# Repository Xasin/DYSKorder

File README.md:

# DYSKorder
What happens if you slap together the Apollo Guidance interface and a few StarTrek inspired interfaces? We'll see!

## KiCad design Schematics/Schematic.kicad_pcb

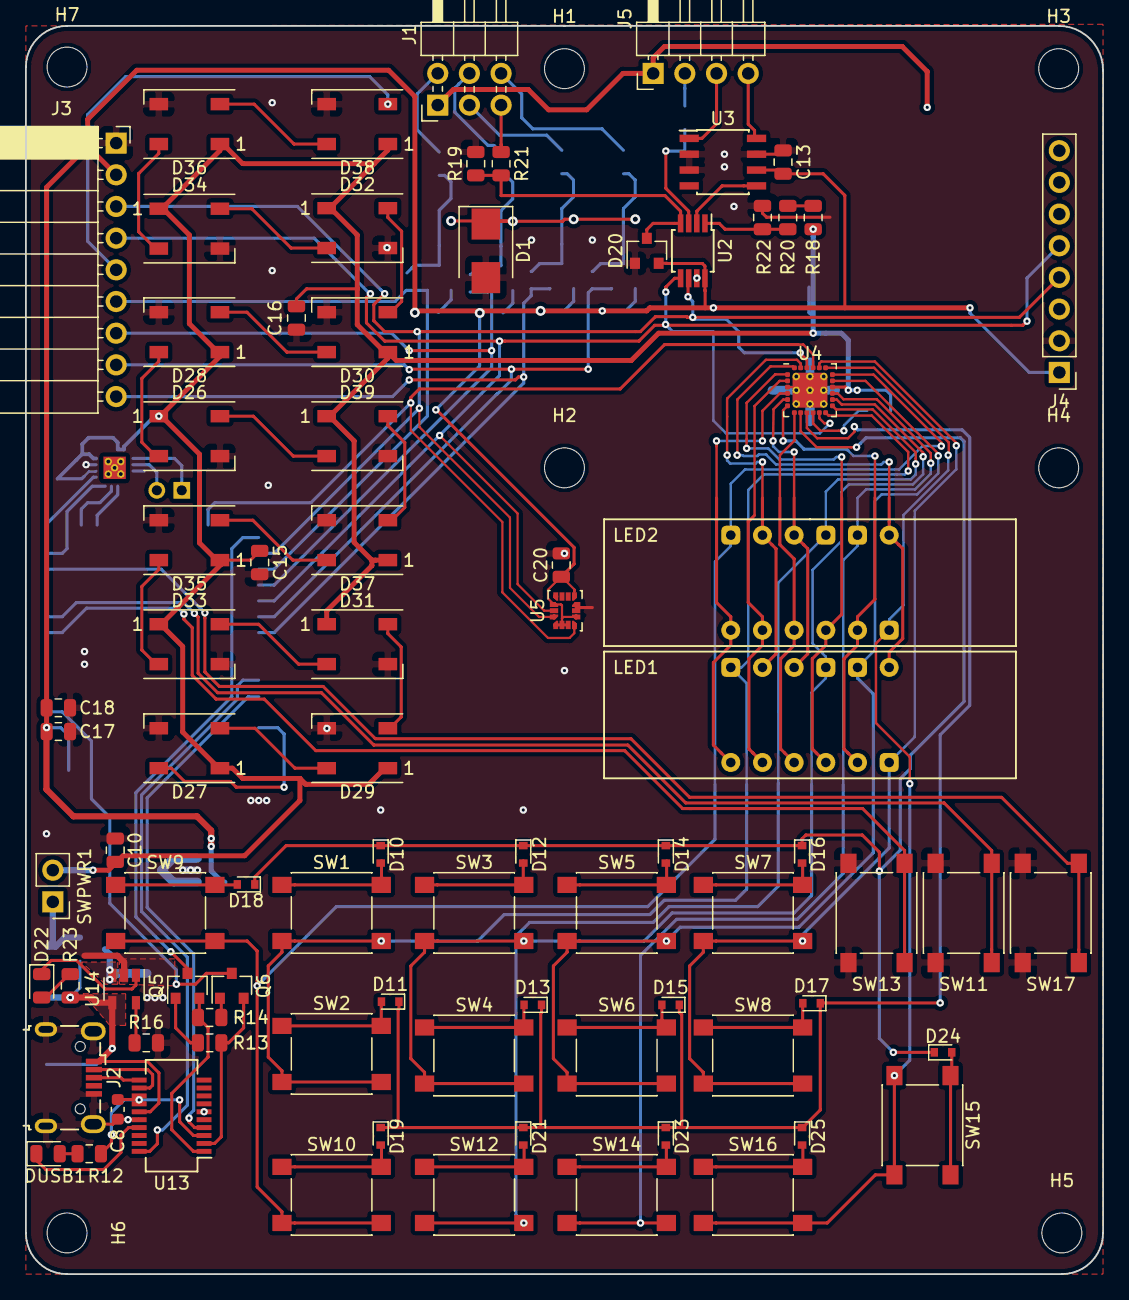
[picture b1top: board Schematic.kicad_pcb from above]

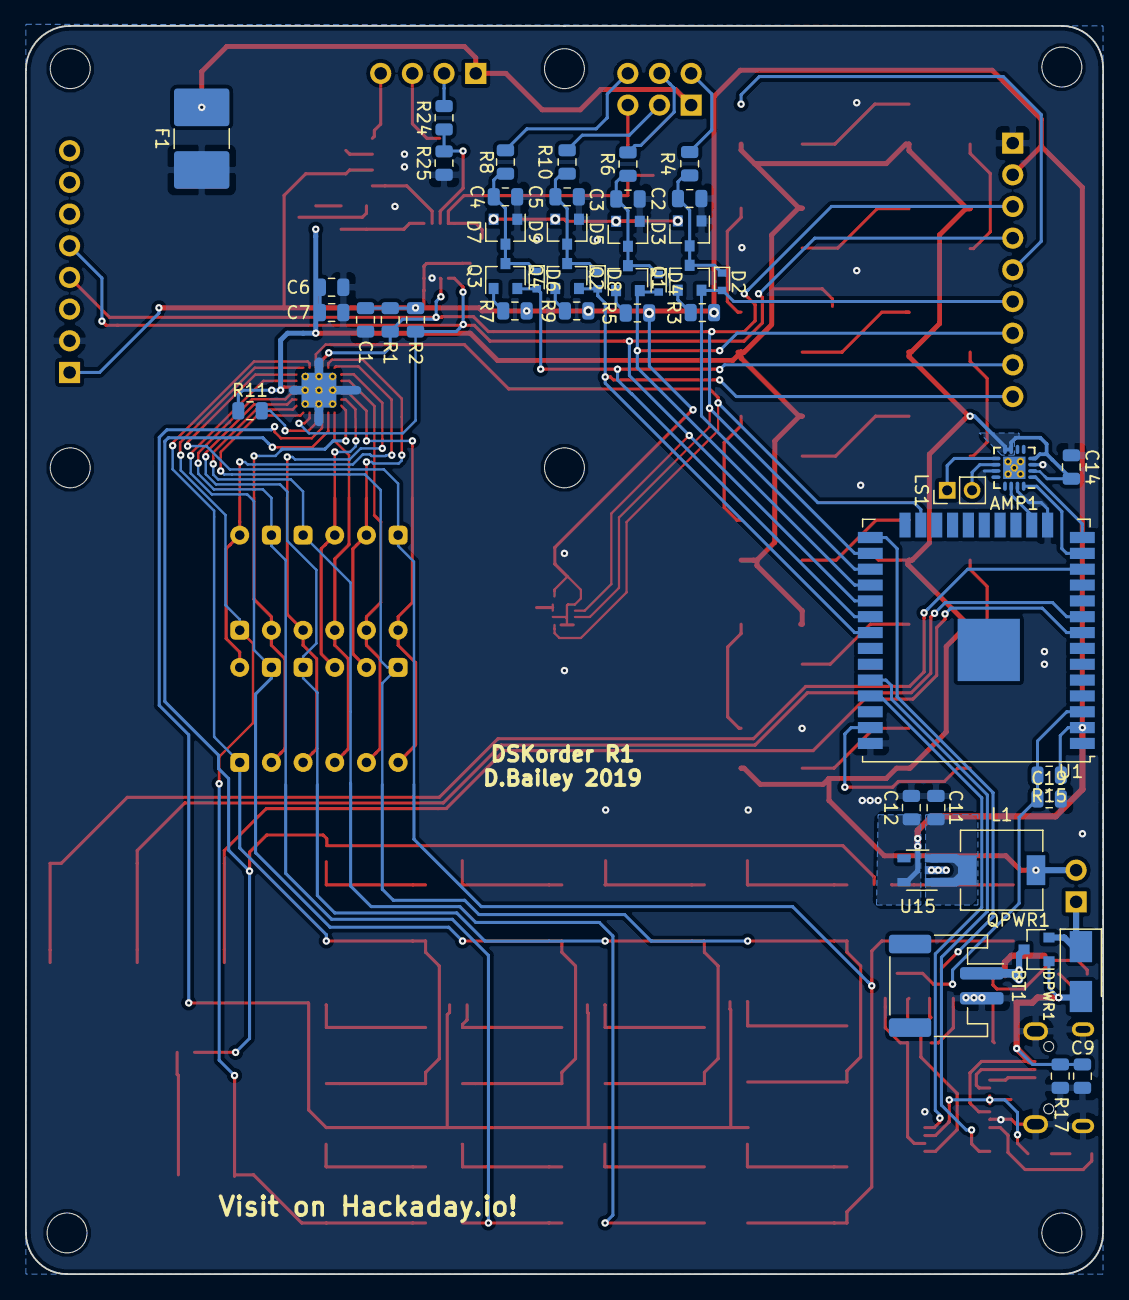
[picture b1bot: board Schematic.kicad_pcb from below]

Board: 2 copper layers, 86.4 x 100.1 mm, 140 parts (50 on the bottom side), 109 nets.

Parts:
AMP1: MAX98357A; QFN-16-1EP_3x3mm_P0.5mm_EP2.7x2.7mm_ThermalVias
BT1: Battery_Cell; JST_PH_S2B-PH-SM4-TB_1x02-1MP_P2.00mm_Horizontal
C1, C6, C13, C15, C16, C18, C20: 0.1uF; C_0805_2012Metric
C2, C3, C4, C5: C_Small; C_0805_2012Metric
C7, C9, C10, C12, C17: 10uF; C_0805_2012Metric
C8: 150nF; C_0603_1608Metric
C11: 150nF; C_0805_2012Metric
C14: 1uF; C_0805_2012Metric
C19: 100nF; C_0805_2012Metric
D1: 14V Breakdown; D_SMB
D2, D4, D6, D8: D_Schottky; D_SOD-523
D3, D5, D7, D9, D20: DB3X313F; SOT-23
D10, D11, D12, D13, D14, D15, D16, D17, D18, D19, D23, D24, D25: D_Small; D_SOD-523
D21: RB521S30T1GOSCT-ND; D_SOD-523
D22: LED; LED_0805_2012Metric
D26, D27, D28, D29, D30, D31, D32, D33, D34, D35, D36, D37, D38, D39: WS2812B; LED_WS2812B_PLCC4_5.0x5.0mm_P3.2mm
DPWR1: D_Schottky; D_SMA
DUSB1: LED; LED_0805_2012Metric
F1: Fuse_Small; Fuse_2816_7142Metric
H1, H2, H3, H4, H5, H6, H7: MountingHole; MountingHole_3.2mm_M3
J1: Conn_02x03_Odd_Even; PinHeader_2x03_P2.54mm_Horizontal
J2: USB_B_Micro; USB_Micro-B_Wuerth_629105150521
J3: Conn_01x09_Female; PinSocket_1x09_P2.54mm_Horizontal
J4: Conn_01x08_Male; PinHeader_1x08_P2.54mm_Vertical
J5: Conn_01x04_Male; PinHeader_1x04_P2.54mm_Horizontal
L1: 100uH; L_6.3x6.3_H3
LED1, LED2: LDQ-M282RI
LS1: Speaker; PinHeader_1x02_P2.00mm_Vertical
Q1, Q2, Q3, Q4, Q5, Q6: Q_NPN_BEC; SOT-23
QPWR1: IRLML6402; SOT-23
R1, R13, R14, R15: R_Small; R_0805_2012Metric
R2, R3, R5, R7, R9, R16, R17: 10k; R_0805_2012Metric
R4, R6, R8, R10, R23: 100R; R_0805_2012Metric
R11: >25k; R_0805_2012Metric
R12: 220; R_0805_2012Metric
R18, R20, R22: 100k; R_0805_2012Metric
R19: 2k; R_0805_2012Metric
R21: 8k; R_0805_2012Metric
R24: 43k; R_0805_2012Metric
R25: 4; R_0805_2012Metric
SW1, SW2, SW3, SW4, SW5, SW6, SW7, SW8, SW9, SW10, SW11, SW12, SW13, SW14, SW15, SW16, SW17: Push; SW_SPST_PTS645
SWPWR1: SW_SPST; PinHeader_1x02_P2.54mm_Vertical
SYM1: SYM_Radioactive_Large; Xas_Logo
SYM2: SYM_Radioactive_Large; Hackaday_Link
U1: ESP32-WROOM-32D; ESP32-WROOM-32U
U2: MAX11613; MSOP-8_3x3mm_P0.65mm
U3: AD8418; SOIC-8_3.9x4.9mm_P1.27mm
U4: AS1115-BQFT; TQFN-24-1EP_4x4mm_P0.5mm_EP2.8x2.8mm_PullBack_ThermalVias
U5: LSM6DS3; LGA-14_3x2.5mm_P0.5mm_LayoutBorder3x4y
U13: FT231XS; SSOP-20_3.9x8.7mm_P0.635mm
U14: MCP73832T-2ACI/OTCT-ND; SOT-23-5
U15: SPX3819M5-L-3-3; SOT-23-5

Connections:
+3V3: C1.1, C12.1, C13.2, C17.1, C18.1, C20.1, D20.2, J3.2, J4.1, R1.1, R2.1, R3.1, R5.1, R7.1, R9.1, R15.1, U1.2, U2.8, U3.6, U5.1, U5.2, U5.3, U5.5, U5.8, U5.12, U15.5
+12P: D1.1, D3.2, D5.2, D7.2, D9.2
+BATT: AMP1.2, AMP1.4, AMP1.7, AMP1.8, C6.1, C7.1, C10.1, C14.2, C15.1, C16.1, D26.1, D27.1, D28.1, D29.1, D30.1, D31.1, D32.1, D33.1, D34.1, D35.1, D36.1, D37.1, D38.1, D39.1, L1.2, R11.1, R18.1, SWPWR1.2, U4.16
/BCLK: AMP1.16, U1.13
/BMode1: SW17.2, U1.12
/BMode2: SW13.2, U1.8
/BMode3: SW11.2, U1.9
/Bat_CHG: R20.2, R22.1, U2.1
/DATA: AMP1.1, U1.14
/E>USB: U1.35, U13.4
/GPIO0: Q5.3, U1.25
/IOGate/UPEXT_BAT: J5.2, R24.2
/IOGate/UPEXT_U: J1.5, R21.1
/IOGate/UPIO1: J1.2, R4.1
/IOGate/UPIO2: J1.4, R6.1
/IOGate/UPIO3: J1.6, R8.1
/IOGate/UPIO4: J1.3, R10.1
/IOGate/UP_GND: F1.2, J1.1, J5.1
/LRCLK: AMP1.14, U1.16
/Power Handling/B_Raw+: BT1.1, QPWR1.3, U14.3
/Power Handling/CHG_Stat: D22.1, U14.1
/RESET: C19.1, Q6.3, R15.2, U1.3
/USB Connection/+5V_USB: C9.2, DPWR1.2, J2.1, QPWR1.1, R17.1, R23.1, U13.15, U14.4
/USB Connection/USB3.3: C8.2, R12.1, U13.3, U13.13, U13.14
/USB>E: U1.34, U13.20
/WS2812_OUT: D27.4, U1.37
BTN_IRQ: U1.23, U4.21, U5.4
GND: AMP1.3, AMP1.11, AMP1.15, BT1.2, C1.2, C2.2, C3.2, C4.2, C5.2, C6.2, C7.2, C8.1, C9.1, C10.2, C11.2, C12.2, C13.1, C14.1, C15.2, C16.2, C17.2, C18.2, C19.2, C20.2, D1.2, D3.1, D5.1, D7.1, D9.1, D20.1, D26.3, D27.3, D28.3, D29.3, D30.3, D31.3, D32.3, D33.3, D34.3, D35.3, D36.3, D37.3, D38.3, D39.3, F1.1, J2.5, J2.6, J3.1, J4.2, R16.2, R17.2, R19.2, R22.2, R25.1, SW11.1, SW13.1, SW17.1, U1.1, U1.15, U1.38, U2.7, U3.2, U3.3, U3.7, U4.3, U4.25, U5.6, U5.7, U13.6, U13.16, U14.2, U15.2
LOCAL_SCL: J3.4, J4.5, R2.2, U1.29, U2.5, U4.11, U5.13
LOCAL_SDA: J3.3, J4.4, R1.2, U1.26, U2.6, U4.22, U5.14
unnamed: AMP1.9, LS1.1
unnamed: AMP1.10, LS1.2
unnamed: C2.1, D2.1, D3.3, Q1.3, R4.2
unnamed: C3.1, D4.1, D5.3, Q2.3, R6.2
unnamed: C4.1, D6.1, D7.3, Q3.3, R8.2
unnamed: C5.1, D8.1, D9.3, Q4.3, R10.2
unnamed: C11.1, L1.1, U15.1, U15.3
unnamed: D10.1, D12.1, D14.1, D16.1, D18.1, D24.1, U4.8
unnamed: D10.2, SW1.1
unnamed: D11.1, D13.1, D15.1, D17.1, D19.1, D21.1, D23.1, D25.1, U4.9
unnamed: D11.2, SW2.1
unnamed: D12.2, SW3.1
unnamed: D13.2, SW4.1
unnamed: D14.2, SW5.1
unnamed: D15.2, SW6.1
unnamed: D16.2, SW7.1
unnamed: D17.2, SW8.1
unnamed: D18.2, SW9.1
unnamed: D19.2, SW10.1
unnamed: D21.2, SW12.1
unnamed: D22.2, R23.2
unnamed: D23.2, SW14.1
unnamed: D24.2, SW15.1
unnamed: D25.2, SW16.1
unnamed: D26.2, D28.4
unnamed: D26.4, D39.2
unnamed: D27.2, D29.4
unnamed: D28.2, D30.4
unnamed: D29.2, D31.4
unnamed: D30.2, D32.4
unnamed: D31.2, D33.4
unnamed: D32.2, D34.4
unnamed: D33.2, D35.4
unnamed: D34.2, D36.4
unnamed: D35.2, D37.4
unnamed: D36.2, D38.4
unnamed: D37.2, D39.4
unnamed: DPWR1.1, QPWR1.2, SWPWR1.1
unnamed: DUSB1.1, U13.17
unnamed: DUSB1.2, R12.2
unnamed: J2.2, U13.12
unnamed: J2.3, U13.11
unnamed: J5.3, U3.1
unnamed: J5.4, U3.8
unnamed: LED1.1, LED2.1, U4.4
unnamed: LED1.2, LED2.2, U4.2
unnamed: LED1.3, LED2.3, U4.7
unnamed: LED1.4, LED2.4, U4.1
unnamed: LED1.5, LED2.5, U4.6
unnamed: LED1.6, SW7.2, SW8.2, U4.20
unnamed: LED1.7, LED2.7, U4.24
unnamed: LED1.8, SW5.2, SW6.2, U4.17
unnamed: LED1.9, SW3.2, SW4.2, U4.14
unnamed: LED1.10, LED2.10, U4.5
unnamed: LED1.11, LED2.11, U4.23
unnamed: LED1.12, SW1.2, SW2.2, U4.12
unnamed: LED2.6, SW15.2, SW16.2, U4.19
unnamed: LED2.8, SW14.2, U4.15
unnamed: LED2.9, SW12.2, U4.13
unnamed: LED2.12, SW9.2, SW10.2, U4.18
unnamed: Q1.1, R3.2
unnamed: Q2.1, R5.2
unnamed: Q3.1, R7.2
unnamed: Q4.1, R9.2
unnamed: Q5.1, R13.1
unnamed: Q5.2, R14.2, U13.1
unnamed: Q6.1, R14.1
unnamed: Q6.2, R13.2, U13.2
unnamed: R11.2, U4.10
unnamed: R16.1, U14.5
unnamed: R18.2, R20.1
PEXT_BAT: R24.1, R25.2, U2.3
PEXT_I: U2.2, U3.5
PEXT_U: D20.3, R19.1, R21.2, U2.4
PIO1: D2.2, J3.6, Q1.2, U1.27
PIO2: D4.2, J3.7, Q2.2, U1.28
PIO3: D6.2, J3.8, Q3.2, U1.30
PIO4: D8.2, J3.9, Q4.2, U1.31
WS2812_EXT: D38.2, J3.5

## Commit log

2019-03-04 Began working on the KiCAD files
2019-03-19 Whheee, parts!
2019-04-02 Set up eclipse workspace
2019-04-03 Got 7-Segments working
2019-04-03 Accellerometer!
2019-04-05 Gyrooooo
2019-04-05 Small tweaks
2019-04-08 Began working on a proper file structure for
2019-04-08 General workings >~>
2019-04-08 Began working on the segment control
2019-04-09 Added IDLE and Floating-point outputs
2019-04-09 Cleaned up how numbers are printed
2019-04-09 Began working on a much neater parameter display method
2019-04-10 Moved DisplayParams out and polished them more :>
2019-04-10 Signals and basic numbers working
2019-04-12 Tweaks and adjustments for cleaner segments
2019-04-12 Added 3D Model of the PCB
2019-04-16 1000Hz tickrate configured
2019-04-16 Began working on the LED indicators
2019-04-16 Set up test Bulbs
2019-04-17 Smal tweaks to the 2Cute detector
2019-04-17 Finalisation of the Bulbs
2019-04-17 Began working on button handling
2019-04-18 Played with a proper console idea
2019-04-21 Added proper ADC smoothing and readouts, tuned bulbs
2019-04-21 Added command line parsing
2019-04-23 Adjusted resistor values
2019-04-24 Added program linked-list class with helper functions
2019-04-24 Testing out program executions
2019-04-25 Added = operator for bulbs and removed button beeps
2019-04-25 Added and used helpers to get user input
2019-04-30 Added bulb convenience and moved graphics away properly
2019-05-01 Moving out the LSM6DS3 to its own library
2019-05-11 Getting those out the way
2019-05-11 Tweaks and programs
2019-05-11 And these are the actual programs
2019-05-11 Added partition table due to program size
2019-05-13 Added a bit more BME interface
2019-05-14 More work on the BME680
2019-05-15 Added wifi command
2019-05-17 Added MQTT output
2019-05-21 Added external Status Bulbs
2019-05-21 Added air quality coloring
2019-05-23 Added fancy background tasking for BME
2019-06-04 Played with fancyschmancy IR Code <3!
2019-06-05 Morge
2019-06-08 Cleanups
2019-06-08 Began working on test cood
2019-06-10 Deleted and moved programs, added MQTT Bypass
2019-06-12 TWEAKS
2019-06-12 GOT THE BEEPS READY>:3
2019-06-13 Fixer-uppered the simon says, added bullshit
2019-06-14 Changed addr to 0 in the meantime
2019-06-20 Added a neat midi player
2019-07-19 Began working on servo and BLDC control
2019-07-26 Added a better motor test
2019-07-29 Tried playing with DShot
2019-09-05 Lots of small tweaks for stuff
2020-11-13 Add ESP libopus component
2020-11-27 Tweak system to use new audio interface
2022-01-08 Remove metadata files
2022-01-08 Add test project (huh?)
